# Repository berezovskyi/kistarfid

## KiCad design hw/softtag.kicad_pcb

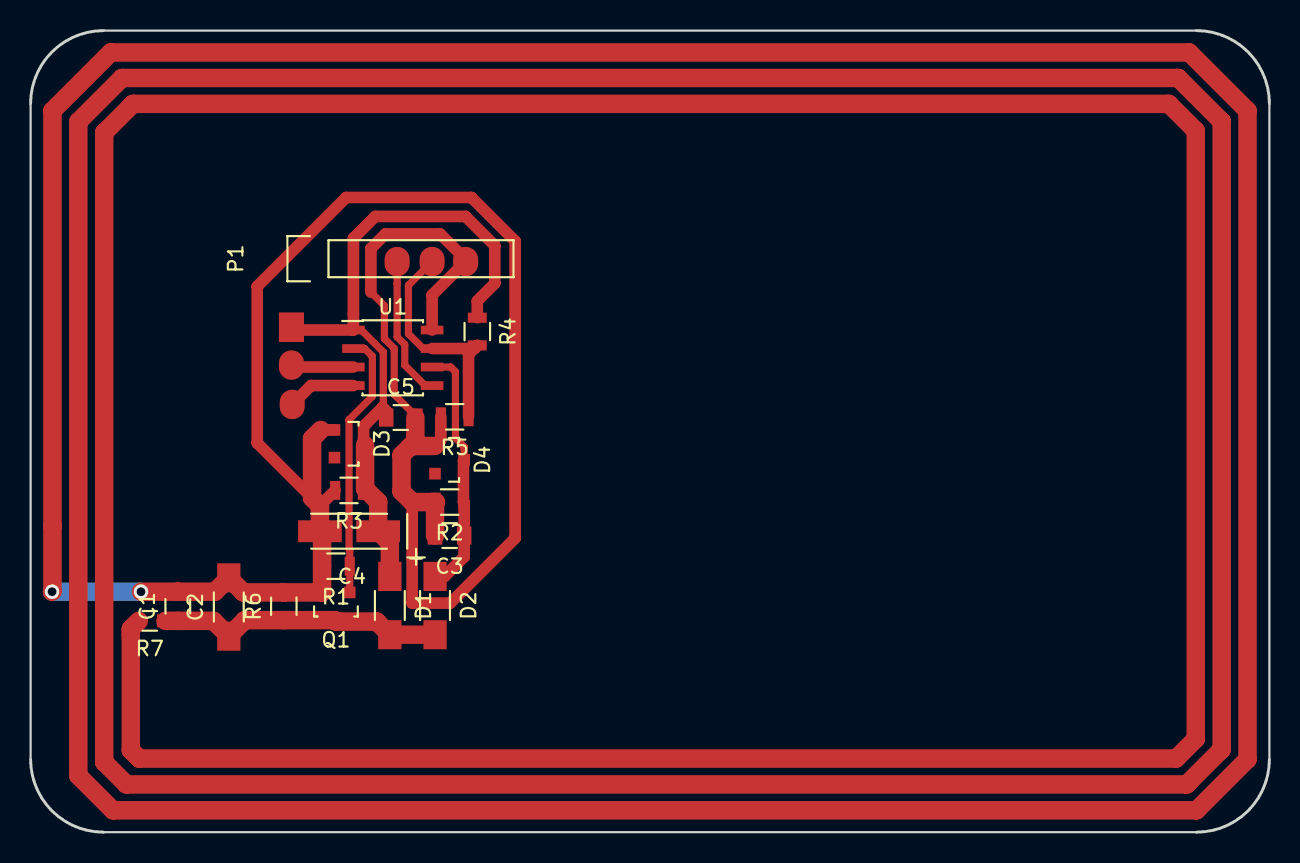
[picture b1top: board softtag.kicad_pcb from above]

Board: 2 copper layers, 85.0 x 55.0 mm, 19 parts (0 on the bottom side), 9 nets.

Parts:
C1, C3, C5: C; C_0805
C2: CTRIM; C_1206_HandSoldering
C4: CP; TantalC_SizeA_EIA-3216_HandSoldering
D1: D_Schottky; C_1206_HandSoldering
D2: D; C_1206_HandSoldering
D3, D4: ZENER; SOT-23
P1: CONN_01X06; Pin_Header_Straight_1x06
Q1: Q_NMOS_GSD; SOT-23
R1, R2, R3, R4, R5, R6: R; R_0805
R7: 0R; R_0603
U1: PIC12LF1612-E/SN; SOIC-8_3.9x4.9mm_Pitch1.27mm

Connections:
/FREE0: P1.2, U1.3
/FREE1: P1.3, U1.4
/FREE2: P1.4, U1.5
/FREE3: P1.5, R4.2, R5.1, U1.7
/MOD_RX: C3.1, D2.1, D4.1, R2.1, U1.6
/MOD_TX: Q1.1, R1.1, U1.2
GND: C1.2, C2.2, C3.2, C4.2, C5.2, D3.2, D4.2, P1.6, Q1.2, R1.2, R2.2, R3.2, R5.2, R6.2, R7.2, U1.8
unnamed: C1.1, C2.1, D1.2, D2.2, Q1.3, R6.1, R7.1
VCC: C4.1, C5.1, D1.1, D3.1, P1.1, R3.1, R4.1, U1.1

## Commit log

2016-09-20 add minutes from today
2016-09-20 update p/n
2016-09-20 add gitignore
2016-09-27 project plan template
2016-09-27 headlines
2016-09-27 words!
2016-10-04 rev A hardware
2016-10-04 Add SW project
2016-10-05 Refactor the project code
2016-10-07 not quite working state machine for decoding
2016-10-07 can now decode one byte
2016-10-07 incorrect bit order when decoding byte
2016-10-08 decode a byte string from reader
2016-10-08 output decoded string as manchester
2016-10-09 managed to generate fairly good modulation frequencies
2016-10-09 can now generate pulse trains for encoding 1:s and 0:s
2016-10-09 modulate start-of-frame and end-of-frame
2016-10-09 hard coded response
2016-10-09 correct response flags
2016-10-11 rolled out bit sending
2016-10-11 modulation kind of works but still not
2016-10-18 added font
2016-10-18 remove blank lines
2016-10-18 ad crc test code
2016-10-18 update code
2016-10-18 Add today's changes, remove ignored files
2016-10-19 Add notes from yesterday
2016-10-19 reformat source
2016-10-25 Add working CRC code
2016-10-25 Make CRC gen dynamic
2016-10-25 Update the CRC SW gen
2016-10-25 arne
2016-10-25 Clean up the code
2016-10-25 Update the schematic
2016-10-25 Reformat code
2016-10-25 Reformat again with K&R w/tabs
2016-10-25 restore tabs
2016-10-25 Split the code across multiple files
2016-10-25 Update main
2016-10-25 update schematic
2016-10-25 add slides plan
2016-10-26 code cleanup
2016-10-26 Reply to read_block with ARNE
2016-10-26 Now we're using CCP1
2016-10-26 update project
2016-10-27 MOD_BIT is very internal and should not be in header
2016-10-27 en liten fuling för accelerometern
2016-10-27 inline
2016-10-27 read command address => adc channel number
2016-10-27 I think this does something
2016-10-27 A window that draws a TrollTag
2016-10-27 interface for reading tag angle
2016-10-27 what the f# is going on?
2016-10-27 oops
2016-10-27 client makefile
2016-10-27 tag rotation kind of works
2016-10-27 non-working inventory
2016-10-28 non-working temperature sensor
2016-10-28 fixed serious memory error in tag angle running average
2016-10-28 prepare for big merge
2016-10-28 fix display
2016-10-28 fix latency maybe
2016-10-28 correct tag id
2016-10-28 got rid of some warnings
2016-10-28 removed custom trigonometry library in favour of atan2
2016-10-29 updated schematic
2016-10-29 added report friendly parts of the schematic
2016-10-29 report template
2016-10-29 removed crap files
2016-10-30 meaurments
2016-10-30 report outline for design
2016-10-30 something something crc
2016-10-30 report mod/demod circuit
2016-10-30 added references
2016-10-30 typo
2016-10-30 added values from notes
2016-10-30 energy harvester
2016-10-30 command decoding
2016-10-30 reponse encoding
2016-10-30 added schematics and block diagrams
2016-10-30 added inductor board layout
2016-10-30 mcu, accelerometer
2016-10-30 title
2016-10-30 added some performance data
2016-10-31 goal
2016-10-31 purpose
2016-10-31 fixed table reference
2016-10-31 flum
2016-10-31 work
2016-10-31 added photo of tag
2016-10-31 derp
2016-10-31 typos
2016-10-31 derps
